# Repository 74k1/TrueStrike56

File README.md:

# TrueStrike56

|  |  |
| --- | --- |

TrueStrike56 is a spin-off from the original [TrueStrike42](https://github.com/byungyoonc/TrueStrike42) with an additional number row and 2 more thumb-keys. Making it a 4x6_4 layout.

# How to build
Refer to the [build guide](hw/rev2/README.md) for detailed instructions.

# Firmware
> [!WARNING]
> MCU will behave very erratic (e.g. sending random keypresses rapidly) right after flashing the firmware, before soldering all the components on the board. This is because MCU's analogue pins are connected to nothing, resulting in noise sensor values. 
>
> Disconnect the MCU from the PC as soon as possible after the successful firmware flash to prevent chaos.

## Use Precompiled Binary
Flash `fw/rev2/truestrike56_via.uf2` to your RP2040 microcontroller in bootloader mode.

## Build on Your Own
### Option A
Copy the `fw/rev2/truestrike56` folder into your cloned QMK Firmware repository's `keyboards` folder, then run `qmk compile -kb truestrike56 -km via`.

### Option B
- [QMK Firmware fork](https://github.com/byungyoonc/qmk_firmware/tree/Truestrike56)
- [VIA QMK Userspace fork](https://github.com/byungyoonc/qmk_userspace_via/tree/truestrike56)

The branches above are from my fork of the QMK Firmware/Userspace repository which supports firmware compilation for TrueStrike56. 

Follow [this guide for External QMK Userspace](https://docs.qmk.fm/newbs_external_userspace) to build it yourself.

# Using VIA HE Configurations
You can access the following tools in VIA by selecting **HE TOOLS**.

## Load VIA Definition
Open `fw/rev2/truestrike56.json` in VIA's **DESIGN** tab to enable VIA support for TrueStrike56.

## Calibrations
**Make sure to run the calibration at least once before using the keyboard!**

### Bottoming Calibration
Calibrates Hall-effect sensor values for each switch when it is fully bottomed out.

Toggle on, fully bottom out each switch, then toggle off.

### Noise Floor Calibration
Calibrates the ambient magnetic flux fluctuation detected by the Hall-effect sensors.

Click once while leaving the keyboard untouched for a brief period. The firmware samples the noise baseline.

### Show Calibration Data
Prints out current calibration data to the debug console.

### Clear Bottoming Calibration Data
Resets Bottoming Calibration Data to prepare for recalibration. Use this when replacing your Hall-effect switches.

## Actuation
### Mode
Choose between APC and Rapid Trigger.

APC works like a traditional digital switch, but you can change where actuation/release occurs.

Rapid Trigger tracks the switch's height to determine whether the key is being pressed down or released.

### Offsets
Sets the offset values for the selected Mode.

The value ranges from 1 (Topmost) to 255 (Bottommost).

# Credits

| Credit | Reason |
| ---: | --- |
| [byungyoonc](https://github.com/byungyoonc) | For the **entire** Engineering of the [PCBs](/hw) (rev1 and rev2) and the Technical side of things (including initial firmware setup) have been done by Byungyoon. |
| [74k1](https://github.com/74k1) | For the commission and the [Case](hw/rev2/case) as well as the small new logo. |

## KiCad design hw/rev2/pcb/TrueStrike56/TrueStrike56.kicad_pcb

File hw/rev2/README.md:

# TrueStrike 56 (Rev 2) - Build Guide

This guide has been written by Tim <74k1>.

## Required

Choose between either a FR-4 Sandwich-Style Case or an Aluminium CNC'd Case.

| Name | Count | Notes |
| --- | --- | --- |
| [Main PCB](hw/rev2/pcb/TrueStrike56/Gerber) | x1 | |
| [Top Aluminium Case](hw/rev2/case/TrueStrike_Case_top_plate.obj) | x1 | For Aluminium Case! |
| [Bottom Aluminium Case](hw/rev2/case/TrueStrike_Case_bottom_plate.obj) | x1 | For Aluminium Case! |
| [Top Plate](hw/rev2/top-plate/) | x1 | For Sandwich-Style Case! |
| [Bottom Case](hw/rev2/bottom-plate/) | x1 | For Sandwich-Style Case! |
| RP2040 dev board with ProMicro compatible pinouts | x1 | You can get one from AliExpress. |
| 128x32 I2C OLED Screen | x1 | |
| EVQWGD001 Encoder | x1 | Get one while the stock still lasts! |
| M2x4mm bolts | x8 | For Aluminium Case! Preferably flat-headed |
| M2x4mm bolts | x16 | For Sandwich-Style Case! Preferably flat-headed |
| M2 7~8mm standoffs | x8 | For Sandwich-Style Case! Cannot have a larger diameter of 3.5mm! (The hexagonal ones won't work!) |
| Some 1mm thick Thermal Pads (not paste) | x1-2 | For Aluminium Case! It'll be used to "bind" the RP2040 with the Aluminium Case. |
| 1U Keycaps of your own choice | x54 | |
| 1.5U Keycaps of your own choice | x2 | |
| HE Switches of your own choice | x56 | |

## Ordering PCB & Case from JLC

### PCBA

I took a small shortcut by ordering the parts including "PCBA".

You can do so too by:

1. Zipping the main PCB folder

  - [Main PCB](hw/rev2/pcb/TrueStrike56/Gerber)

2. Upload the PCB to JLC's Standard PCB/PCBA for a quote and follow these settings:

3. Continue. You will eventually have to upload the [BOM](hw/rev2/TrueStrike56/production/bom.csv) and [Positions](hw/rev2/TrueStrike56/production/positions.csv) file.

4. Continue. The error only shows the missing RP2040, OLED and our Scrolling Encoder.

5. Hit the two boxes. Then search for missing parts:

6. Enter `74HC4051D,653-JSM` into the search field, and select the only part shown

7. Your final BOM should look like this:

8. On the next screen, you'll see some components misplaced / not rotated. (Zoomed in image for reference)

9. You'll want to select the following and then hit the rotate button twice.

10. That's it for the PCBA. With the correct Category, you can then save it to cart.

### Cases

Depending on whether it's the Sandwich-Style Case or the Aluminium Case, you either:

| Sandwich-Style Case | Aluminium Case |
| --- | --- |
| You upload the following files to the PCB Quote site.<br>Just keep the defaults / choose your own color. | You upload the following files to the CNC Quote site.<br>Feel free to adjust the finish to your liking. (In my case, I did Aluminium 6061, Bead Blasting + Anodizing, Dark Green, Matte, Tight Test Tolerance at +-0.10mm)<br><br>One note, you'll need to add the "Threads" service to the top half of the case. The technical drawing is attached. |
| You'll need to Zip these folders again:<br>- [Top Plate](hw/rev2/top-plate/Gerber)<br>- [Bottom Case](hw/rev2/bottom-plate/Gerber) |- [Aluminium Top](hw/rev2/case/TrueStrike_Case_top_plate.step)<br>- [Technical Drawing for Threads](hw/rev2/case/TrueStrike_Case_Technical_drawing.pdf)<br>- [Aluminium Bottom](hw/rev2/case/TrueStrike_Case_bottom_plate.step) |

## Assembly

Assembly is quite straightforward. A few hints based on what to do first though:

1. Make sure to flash either the default firmware onto the RP2040 board or your own, BEFORE you solder it to the PCB, as the RP2040 RST buttons on the RP2040 Pro Micro board won't be accessible after soldering.
2. If Aluminium Case: Cut and adjust the Thermal Pads onto the Board before soldering. (between PCB and RP2040 Pro Micro)
3. Add EVQWGD001 and OLED screen to the PCB (it'd make sense to put electrical tape between the RP2040 PCB and the OLED Screen)
  - NOTE: The EVQWGD001 hole on the PCB is very tight. You'll have to bend the pins a little bit to make it fit very snug. As a tip: start with the plastic part, then the pins.
4. Add your Switches to the top plate
5. If Aluminium Case: Cut and adjust the rest of the Thermal Pads between the bottom plate and the PCB.
6. Afterwards, it's pretty self-explanatory from here on out.

## Questions

Should you have questions, feel free to contact either of us.
I currently don't accept commissions to build a keyboard for you.

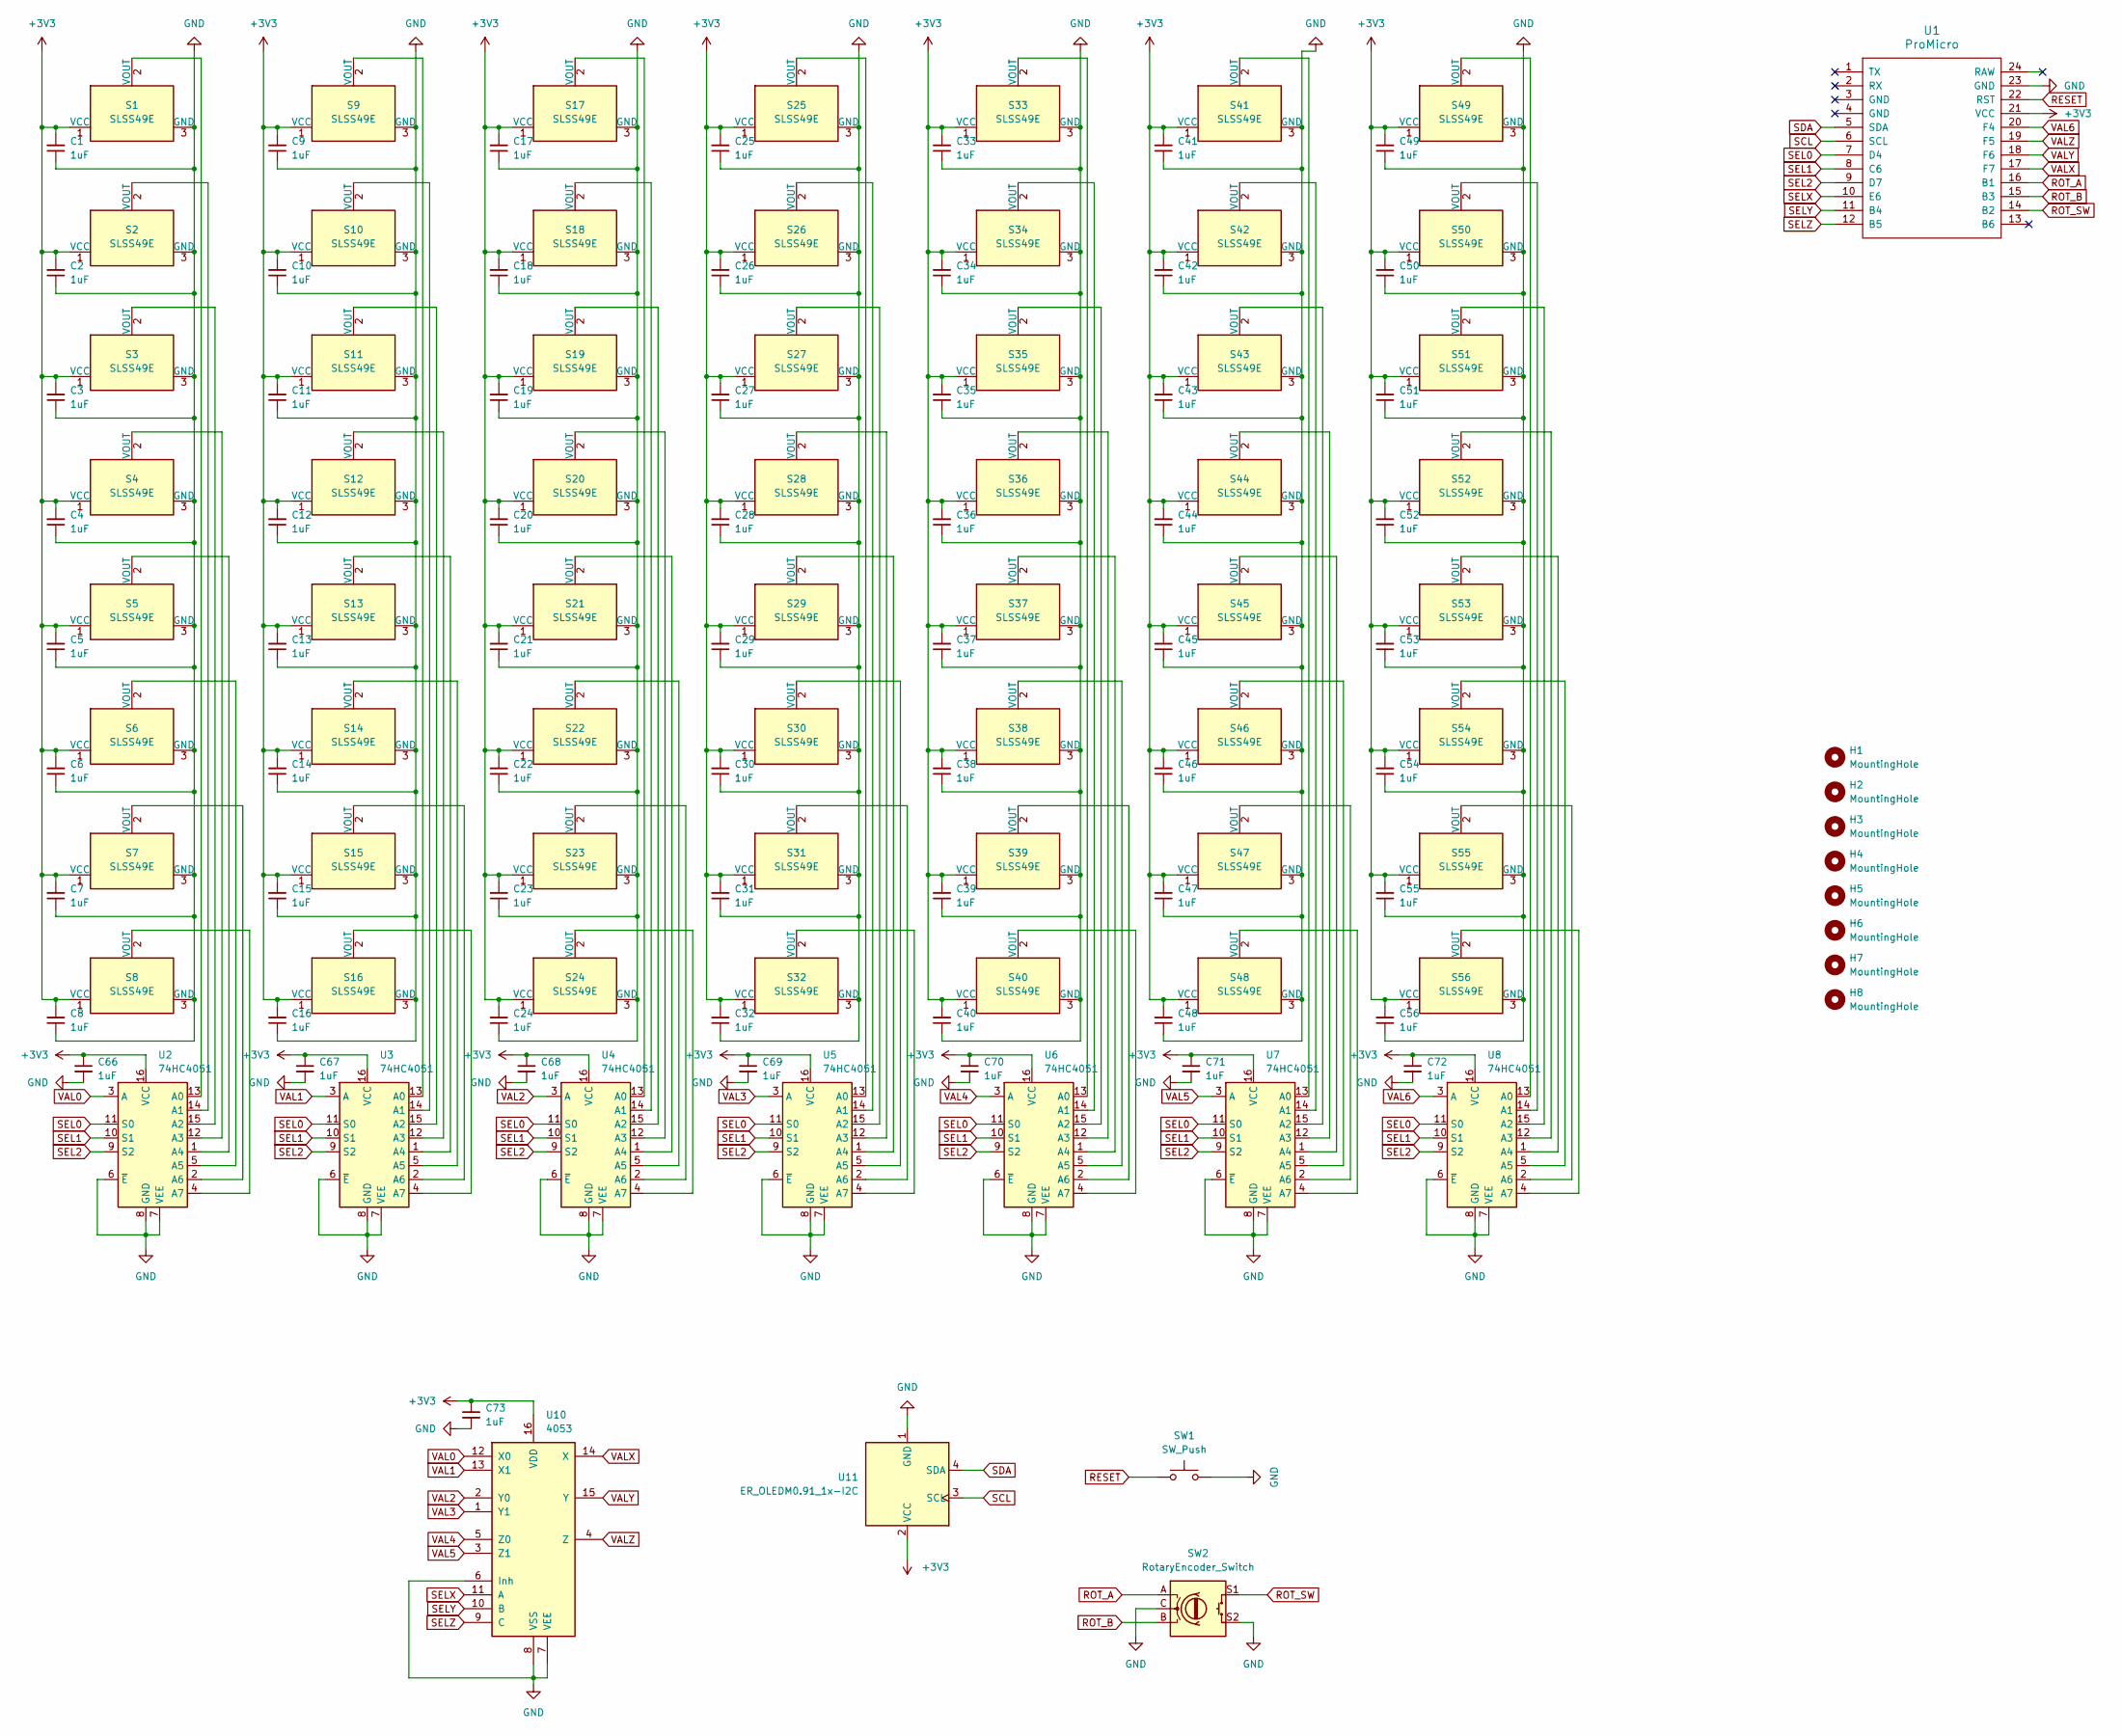
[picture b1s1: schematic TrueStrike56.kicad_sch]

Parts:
C1, C2, C3, C4, C5, C6, C7, C8, C9, C10, C11, C12, C13, C14, C15, C16, C17, C18, C19, C20, C21, C22, C23, C24, C25, C26, C27, C28, C29, C30, C31, C32, C33, C34, C35, C36, C37, C38, C39, C40, C41, C42, C43, C44, C45, C46, C47, C48, C49, C50, C51, C52, C53, C54, C55, C56, C66, C67, C68, C69, C70, C71, C72, C73: 1uF; C_0805_2012Metric_Pad1.18x1.45mm_HandSolder; LCSC Part # C28233
H1, H2, H3, H4, H5, H6, H7, H8: MountingHole; MountingHole_3.5mm
S1, S2, S3, S4, S5, S6, S7, S8, S9, S10, S11, S12, S13, S14, S15, S16, S17, S18, S19, S20, S21, S22, S23, S24, S25, S26, S27, S28, S29, S30, S31, S32, S33, S34, S35, S36, S37, S38, S39, S40, S41, S42, S43, S44, S45, S46, S47, S48, S49, S50, S51, S54, S55, S56: SLSS49E; HE-Switch-1U; LCSC Part # C126669
S52, S53: SLSS49E; HE-Switch-1.5U; LCSC Part # C126669
SW1: SW_Push; SW_Push_1P1T_XKB_TS-1187A; LCSC Part # C318884
SW2: RotaryEncoder_Switch; RollerEncoder_Panasonic_EVQWGD001
U1: ProMicro
U2, U3, U4, U5, U6, U7, U8: 74HC4051; SOIC-16_3.9x9.9mm_P1.27mm; LCSC Part # C85220
U10: 4053; SOIC-16_3.9x9.9mm_P1.27mm; LCSC Part # C5647
U11: ER_OLEDM0.91_1x-I2C

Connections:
+3V3: C1.2, C2.2, C3.2, C4.2, C5.2, C6.2, C7.2, C8.2, C9.2, C10.2, C11.2, C12.2, C13.2, C14.2, C15.2, C16.2, C17.2, C18.2, C19.2, C20.2, C21.2, C22.2, C23.2, C24.2, C25.2, C26.2, C27.2, C28.2, C29.2, C30.2, C31.2, C32.2, C33.2, C34.2, C35.2, C36.2, C37.2, C38.2, C39.2, C40.2, C41.2, C42.2, C43.2, C44.2, C45.2, C46.2, C47.2, C48.2, C49.2, C50.2, C51.2, C52.2, C53.2, C54.2, C55.2, C56.2, C66.1, C67.1, C68.1, C69.1, C70.1, C71.1, C72.1, C73.1, S1.1 (VCC), S2.1 (VCC), S3.1 (VCC), S4.1 (VCC), S5.1 (VCC), S6.1 (VCC), S7.1 (VCC), S8.1 (VCC), S9.1 (VCC), S10.1 (VCC), S11.1 (VCC), S12.1 (VCC), S13.1 (VCC), S14.1 (VCC), S15.1 (VCC), S16.1 (VCC), S17.1 (VCC), S18.1 (VCC), S19.1 (VCC), S20.1 (VCC), S21.1 (VCC), S22.1 (VCC), S23.1 (VCC), S24.1 (VCC), S25.1 (VCC), S26.1 (VCC), S27.1 (VCC), S28.1 (VCC), S29.1 (VCC), S30.1 (VCC), S31.1 (VCC), S32.1 (VCC), S33.1 (VCC), S34.1 (VCC), S35.1 (VCC), S36.1 (VCC), S37.1 (VCC), S38.1 (VCC), S39.1 (VCC), S40.1 (VCC), S41.1 (VCC), S42.1 (VCC), S43.1 (VCC), S44.1 (VCC), S45.1 (VCC), S46.1 (VCC), S47.1 (VCC), S48.1 (VCC), S49.1 (VCC), S50.1 (VCC), S51.1 (VCC), S52.1 (VCC), S53.1 (VCC), S54.1 (VCC), S55.1 (VCC), S56.1 (VCC), U1.21 (VCC), U2.16 (VCC), U3.16 (VCC), U4.16 (VCC), U5.16 (VCC), U6.16 (VCC), U7.16 (VCC), U8.16 (VCC), U10.16 (VDD), U11.2 (VCC)
GND: C1.1, C2.1, C3.1, C4.1, C5.1, C6.1, C7.1, C8.1, C9.1, C10.1, C11.1, C12.1, C13.1, C14.1, C15.1, C16.1, C17.1, C18.1, C19.1, C20.1, C21.1, C22.1, C23.1, C24.1, C25.1, C26.1, C27.1, C28.1, C29.1, C30.1, C31.1, C32.1, C33.1, C34.1, C35.1, C36.1, C37.1, C38.1, C39.1, C40.1, C41.1, C42.1, C43.1, C44.1, C45.1, C46.1, C47.1, C48.1, C49.1, C50.1, C51.1, C52.1, C53.1, C54.1, C55.1, C56.1, C66.2, C67.2, C68.2, C69.2, C70.2, C71.2, C72.2, C73.2, S1.3 (GND), S2.3 (GND), S3.3 (GND), S4.3 (GND), S5.3 (GND), S6.3 (GND), S7.3 (GND), S8.3 (GND), S9.3 (GND), S10.3 (GND), S11.3 (GND), S12.3 (GND), S13.3 (GND), S14.3 (GND), S15.3 (GND), S16.3 (GND), S17.3 (GND), S18.3 (GND), S19.3 (GND), S20.3 (GND), S21.3 (GND), S22.3 (GND), S23.3 (GND), S24.3 (GND), S25.3 (GND), S26.3 (GND), S27.3 (GND), S28.3 (GND), S29.3 (GND), S30.3 (GND), S31.3 (GND), S32.3 (GND), S33.3 (GND), S34.3 (GND), S35.3 (GND), S36.3 (GND), S37.3 (GND), S38.3 (GND), S39.3 (GND), S40.3 (GND), S41.3 (GND), S42.3 (GND), S43.3 (GND), S44.3 (GND), S45.3 (GND), S46.3 (GND), S47.3 (GND), S48.3 (GND), S49.3 (GND), S50.3 (GND), S51.3 (GND), S52.3 (GND), S53.3 (GND), S54.3 (GND), S55.3 (GND), S56.3 (GND), SW1.2, SW2.C, SW2.S2, U1.23 (GND), U2.6 (~E), U2.7 (VEE), U2.8 (GND), U3.6 (~E), U3.7 (VEE), U3.8 (GND), U4.6 (~E), U4.7 (VEE), U4.8 (GND), U5.6 (~E), U5.7 (VEE), U5.8 (GND), U6.6 (~E), U6.7 (VEE), U6.8 (GND), U7.6 (~E), U7.7 (VEE), U7.8 (GND), U8.6 (~E), U8.7 (VEE), U8.8 (GND), U10.6 (Inh), U10.7 (VEE), U10.8 (VSS), U11.1 (GND)
unnamed: S1.2 (VOUT), U2.13 (A0)
unnamed: S2.2 (VOUT), U2.14 (A1)
unnamed: S3.2 (VOUT), U2.15 (A2)
unnamed: S4.2 (VOUT), U2.12 (A3)
unnamed: S5.2 (VOUT), U2.1 (A4)
unnamed: S6.2 (VOUT), U2.5 (A5)
unnamed: S7.2 (VOUT), U2.2 (A6)
unnamed: S8.2 (VOUT), U2.4 (A7)
unnamed: S9.2 (VOUT), U3.13 (A0)
unnamed: S10.2 (VOUT), U3.14 (A1)
unnamed: S11.2 (VOUT), U3.15 (A2)
unnamed: S12.2 (VOUT), U3.12 (A3)
unnamed: S13.2 (VOUT), U3.1 (A4)
unnamed: S14.2 (VOUT), U3.5 (A5)
unnamed: S15.2 (VOUT), U3.2 (A6)
unnamed: S16.2 (VOUT), U3.4 (A7)
unnamed: S17.2 (VOUT), U4.13 (A0)
unnamed: S18.2 (VOUT), U4.14 (A1)
unnamed: S19.2 (VOUT), U4.15 (A2)
unnamed: S20.2 (VOUT), U4.12 (A3)
unnamed: S21.2 (VOUT), U4.1 (A4)
unnamed: S22.2 (VOUT), U4.5 (A5)
unnamed: S23.2 (VOUT), U4.2 (A6)
unnamed: S24.2 (VOUT), U4.4 (A7)
unnamed: S25.2 (VOUT), U5.13 (A0)
unnamed: S26.2 (VOUT), U5.14 (A1)
unnamed: S27.2 (VOUT), U5.15 (A2)
unnamed: S28.2 (VOUT), U5.12 (A3)
unnamed: S29.2 (VOUT), U5.1 (A4)
unnamed: S30.2 (VOUT), U5.5 (A5)
unnamed: S31.2 (VOUT), U5.2 (A6)
unnamed: S32.2 (VOUT), U5.4 (A7)
unnamed: S33.2 (VOUT), U6.13 (A0)
unnamed: S34.2 (VOUT), U6.14 (A1)
unnamed: S35.2 (VOUT), U6.15 (A2)
unnamed: S36.2 (VOUT), U6.12 (A3)
unnamed: S37.2 (VOUT), U6.1 (A4)
unnamed: S38.2 (VOUT), U6.5 (A5)
unnamed: S39.2 (VOUT), U6.2 (A6)
unnamed: S40.2 (VOUT), U6.4 (A7)
unnamed: S41.2 (VOUT), U7.13 (A0)
unnamed: S42.2 (VOUT), U7.14 (A1)
unnamed: S43.2 (VOUT), U7.15 (A2)
unnamed: S44.2 (VOUT), U7.12 (A3)
unnamed: S45.2 (VOUT), U7.1 (A4)
unnamed: S46.2 (VOUT), U7.5 (A5)
unnamed: S47.2 (VOUT), U7.2 (A6)
unnamed: S48.2 (VOUT), U7.4 (A7)
unnamed: S49.2 (VOUT), U8.13 (A0)
unnamed: S50.2 (VOUT), U8.14 (A1)
unnamed: S51.2 (VOUT), U8.15 (A2)
unnamed: S52.2 (VOUT), U8.12 (A3)
unnamed: S53.2 (VOUT), U8.1 (A4)
unnamed: S54.2 (VOUT), U8.5 (A5)
unnamed: S55.2 (VOUT), U8.2 (A6)
unnamed: S56.2 (VOUT), U8.4 (A7)
RESET: SW1.1, U1.22 (RST)
ROT_A: SW2.A, U1.16 (B1)
ROT_B: SW2.B, U1.15 (B3)
ROT_SW: SW2.S1, U1.14 (B2)
SCL: U1.6 (SCL), U11.3 (SCL)
SDA: U1.5 (SDA), U11.4 (SDA)
SEL0: U1.7 (D4), U2.11 (S0), U3.11 (S0), U4.11 (S0), U5.11 (S0), U6.11 (S0), U7.11 (S0), U8.11 (S0)
SEL1: U1.8 (C6), U2.10 (S1), U3.10 (S1), U4.10 (S1), U5.10 (S1), U6.10 (S1), U7.10 (S1), U8.10 (S1)
SEL2: U1.9 (D7), U2.9 (S2), U3.9 (S2), U4.9 (S2), U5.9 (S2), U6.9 (S2), U7.9 (S2), U8.9 (S2)
SELX: U1.10 (E6), U10.11 (A)
SELY: U1.11 (B4), U10.10 (B)
SELZ: U1.12 (B5), U10.9 (C)
VAL0: U2.3 (A), U10.12 (X0)
VAL1: U3.3 (A), U10.13 (X1)
VAL2: U4.3 (A), U10.2 (Y0)
VAL3: U5.3 (A), U10.1 (Y1)
VAL4: U6.3 (A), U10.5 (Z0)
VAL5: U7.3 (A), U10.3 (Z1)
VAL6: U1.20 (F4), U8.3 (A)
VALX: U1.17 (F7), U10.14 (X)
VALY: U1.18 (F6), U10.15 (Y)
VALZ: U1.19 (F5), U10.4 (Z)

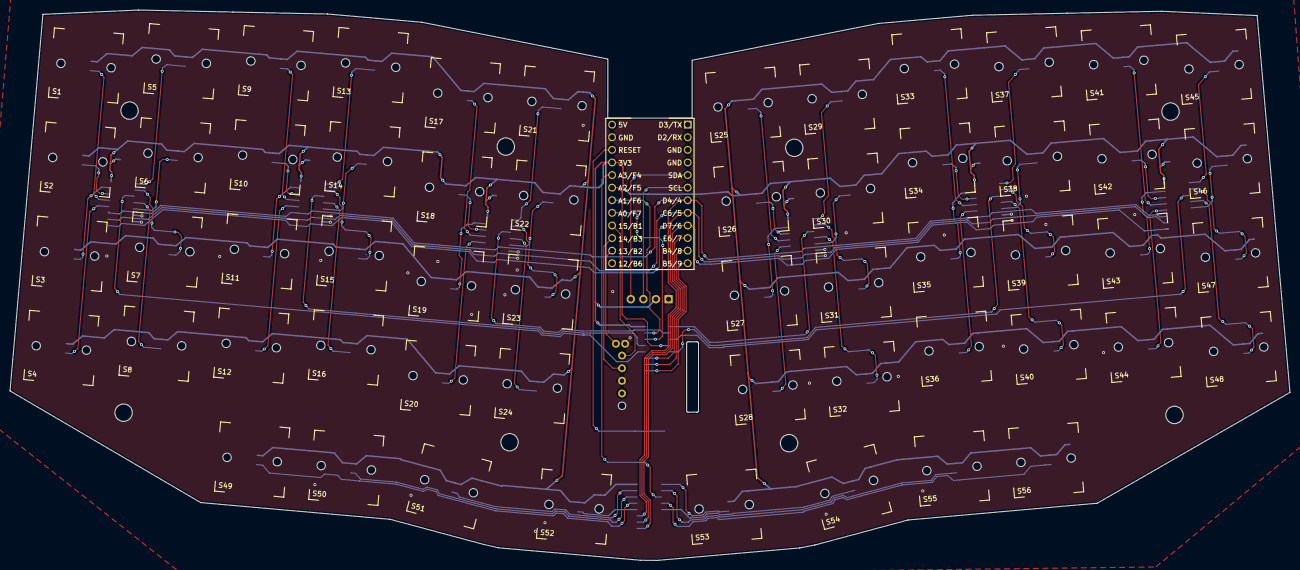
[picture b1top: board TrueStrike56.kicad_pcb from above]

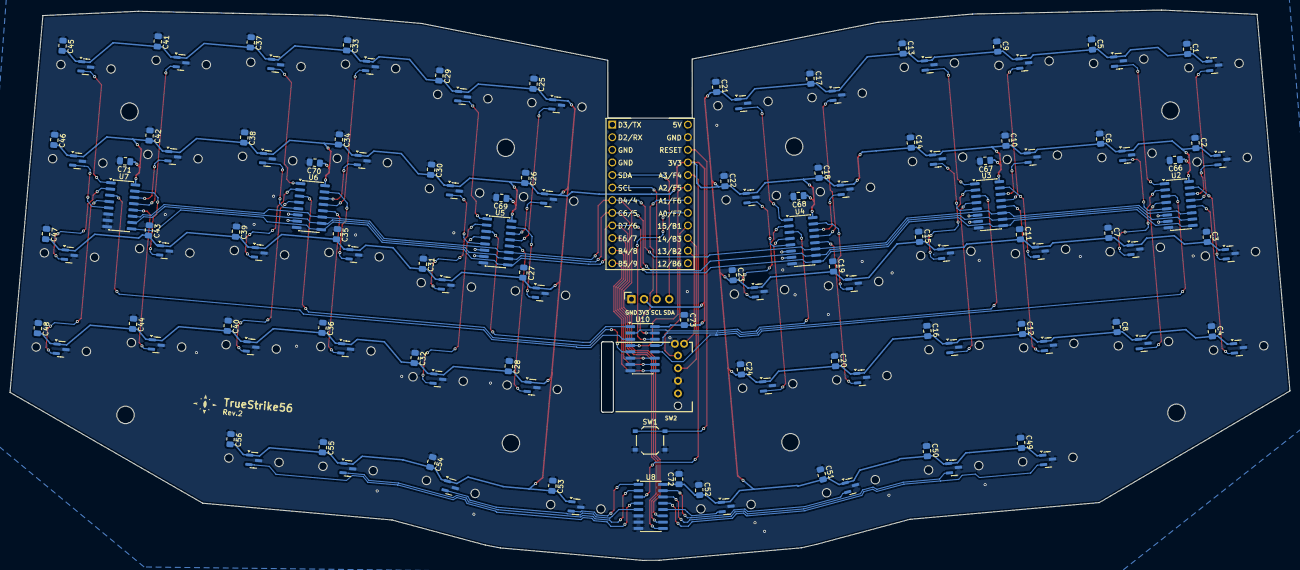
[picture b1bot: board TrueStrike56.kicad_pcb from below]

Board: 2 copper layers, 258.0 x 110.9 mm, 140 parts (130 on the bottom side), 80 nets.

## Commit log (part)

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2026-06-20 Move existing hardware files under rev1
2026-06-20 Add rev2 hw project
2026-06-20 Add mounting holes to PCB
